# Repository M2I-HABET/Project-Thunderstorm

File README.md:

Project Thunderstorm
==================

Project Thunderstorm aims to launch high altitude balloons into thunderstorms in order to collect data. Multiple balloons will be launched to take data points at different points in the thunderstorm and to use a mesh network to help deliver information throughout the thunderstorm.

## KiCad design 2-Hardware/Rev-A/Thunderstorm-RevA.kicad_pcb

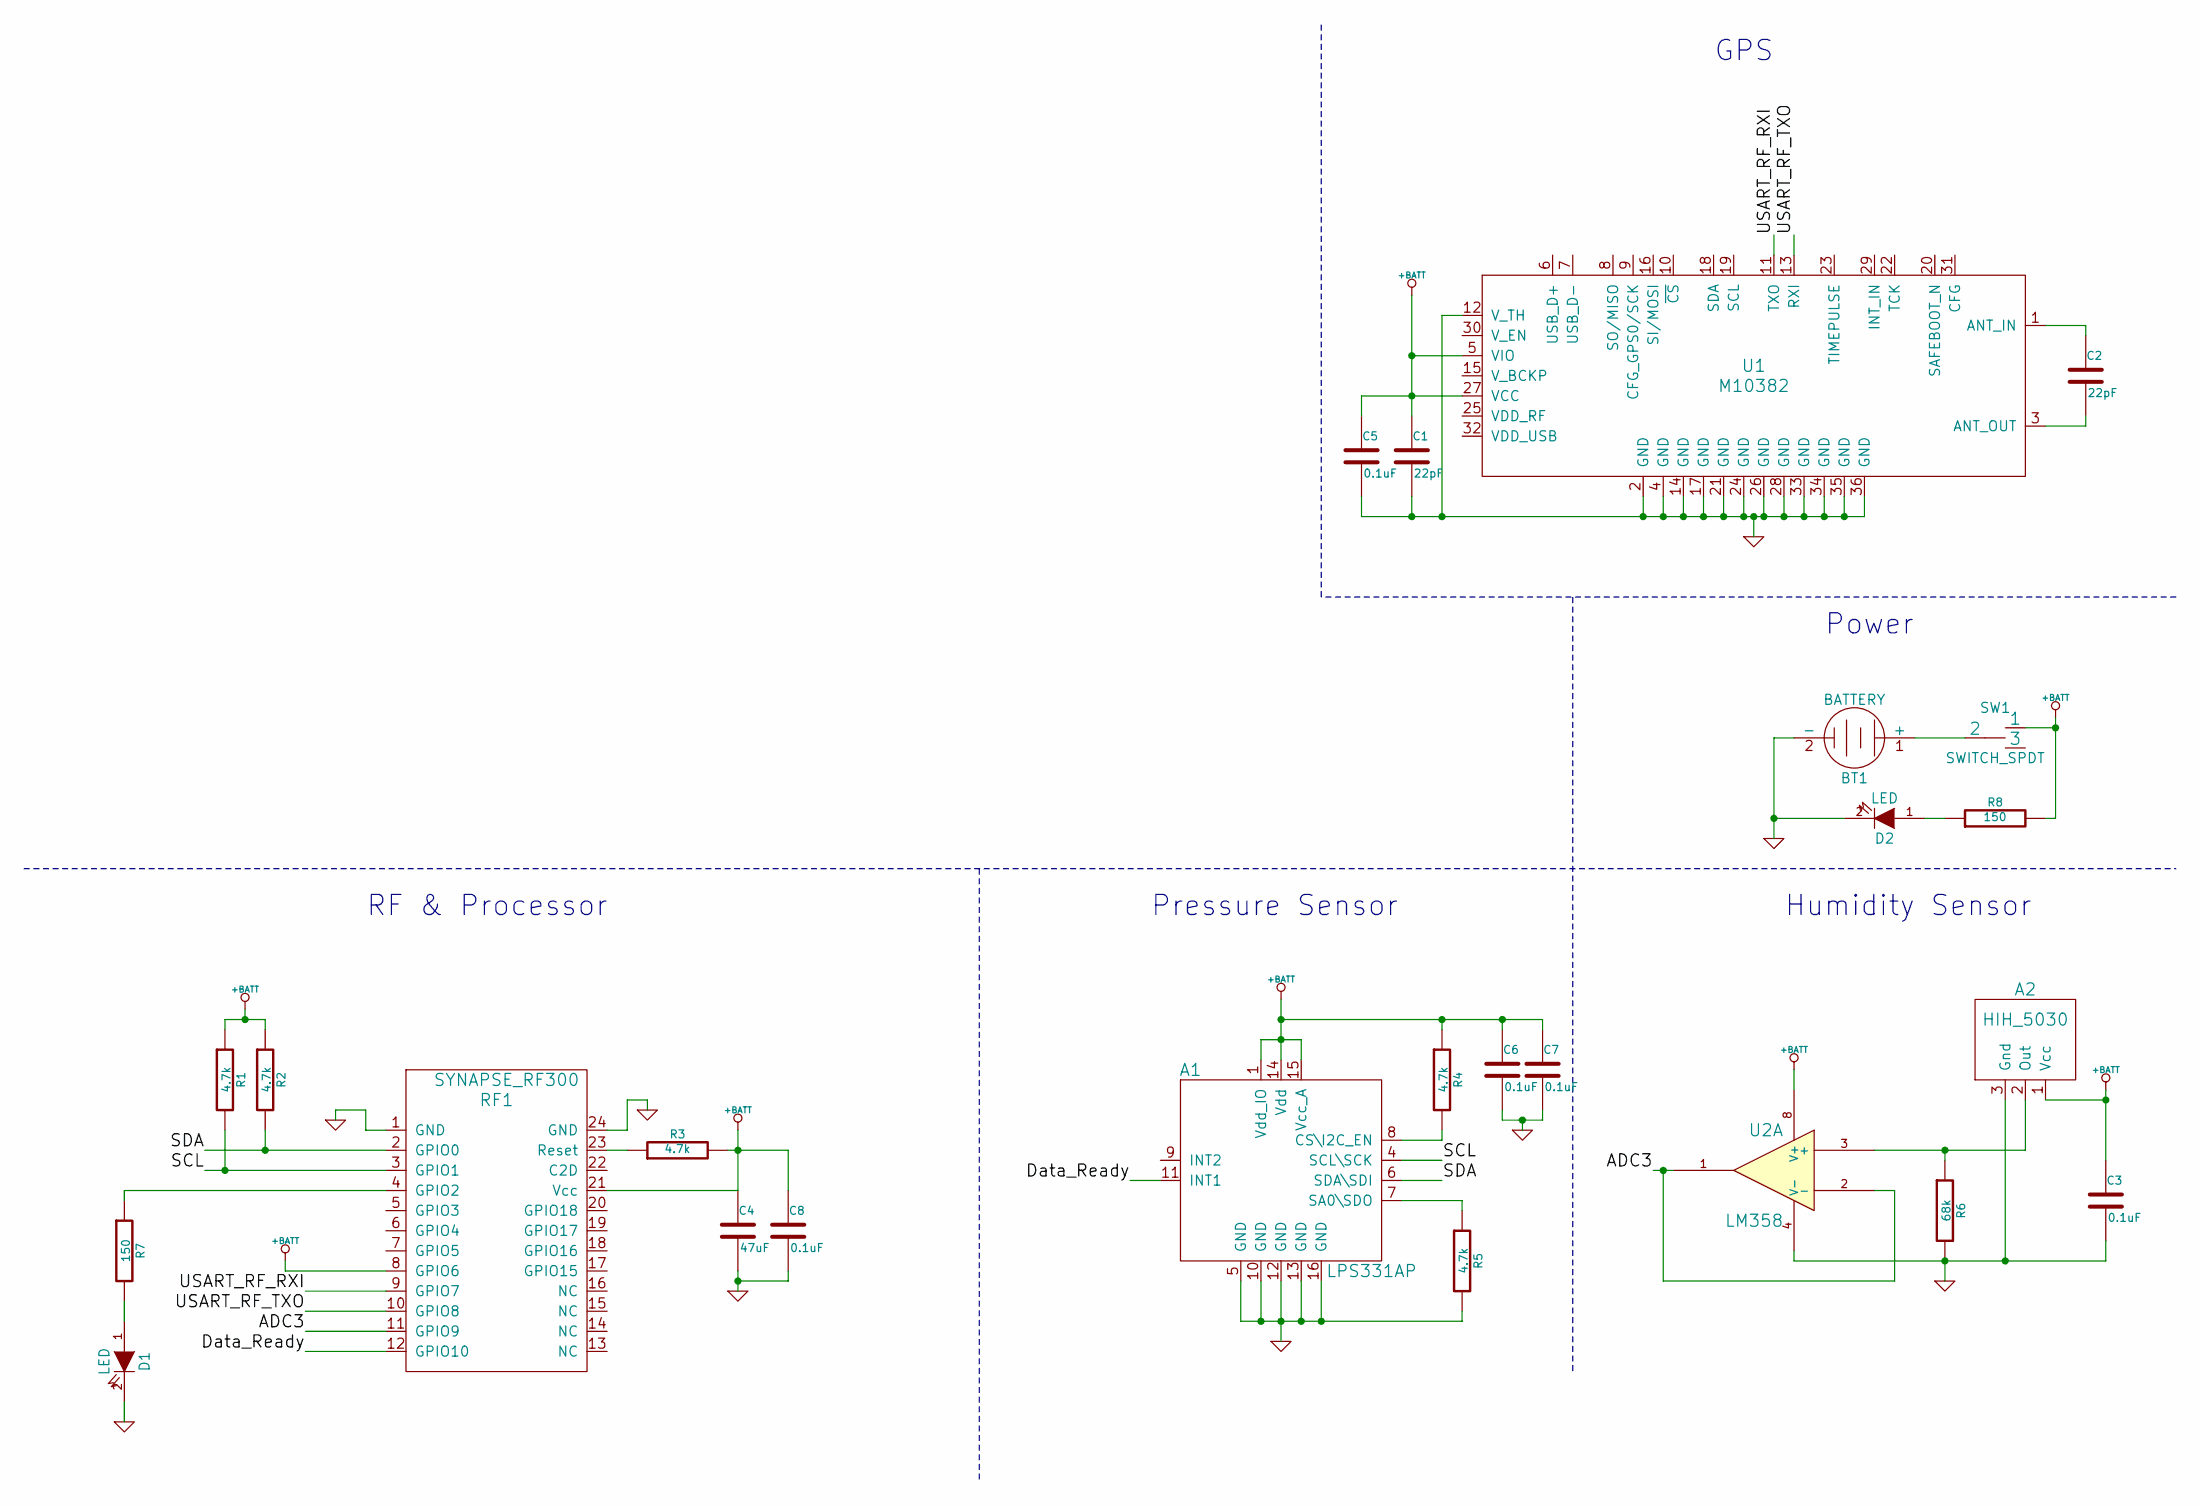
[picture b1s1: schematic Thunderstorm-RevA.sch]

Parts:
A1: LPS331AP
A2: HIH_5030
BT1: BATTERY
C1, C2: 22pF
C3, C5, C6, C7, C8: 0.1uF
C4: 47uF
D1, D2: LED
R1, R2, R3, R4, R5: 4.7k
R6: 68k
R7, R8: 150
RF1: SYNAPSE_RF300
SW1: SWITCH_SPDT
U1: M10382
U2: LM358

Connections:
+BATT: A1.1 (Vdd_IO), A1.14 (Vdd), A1.15 (Vcc_A), A2.1 (Vcc), C1.1, C3.1, C4.1, C5.1, C6.1, C7.1, C8.1, R1.1, R2.1, R3.2, R4.1, R8.2, RF1.8 (GPIO6), RF1.21 (Vcc), SW1.1, U1.5 (VIO), U1.27 (VCC), U2.8 (V+)
/ADC3: RF1.11 (GPIO9), U2.1, U2.2 (-)
/Data_Ready: A1.11 (INT1), RF1.12 (GPIO10)
/SCL: A1.4 (SCL\SCK), R1.2, RF1.3 (GPIO1)
/SDA: A1.6 (SDA\SDI), R2.2, RF1.2 (GPIO0)
/USART_RF_RXI: RF1.9 (GPIO7), U1.11 (TXO)
/USART_RF_TXO: RF1.10 (GPIO8), U1.13 (RXI)
GND: A1.5 (GND), A1.10 (GND), A1.12 (GND), A1.13 (GND), A1.16 (GND), A2.3 (Gnd), BT1.2 (-), C1.2, C3.2, C4.2, C5.2, C6.2, C7.2, C8.2, D1.2 (K), D2.2 (K), R5.2, R6.2, RF1.1 (GND), RF1.24 (GND), U1.2 (GND), U1.4 (GND), U1.12 (V_TH), U1.14 (GND), U1.17 (GND), U1.21 (GND), U1.24 (GND), U1.26 (GND), U1.28 (GND), U1.33 (GND), U1.34 (GND), U1.35 (GND), U1.36 (GND), U2.4 (V-)
unnamed: A1.7 (SA0\SDO), R5.1
unnamed: A1.8 (CS\I2C_EN), R4.2
unnamed: C2.2, U1.3 (ANT_OUT)
unnamed: C2.1, U1.1 (ANT_IN)
unnamed: A2.2 (Out), R6.1, U2.3 (+)
unnamed: R7.1, RF1.4 (GPIO2)
unnamed: D1.1 (A), R7.2
unnamed: D2.1 (A), R8.1
unnamed: R3.1, RF1.23 (Reset)
unnamed: BT1.1 (+), SW1.2

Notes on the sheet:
Humidity Sensor
GPS
RF & Processor
Power
Pressure Sensor

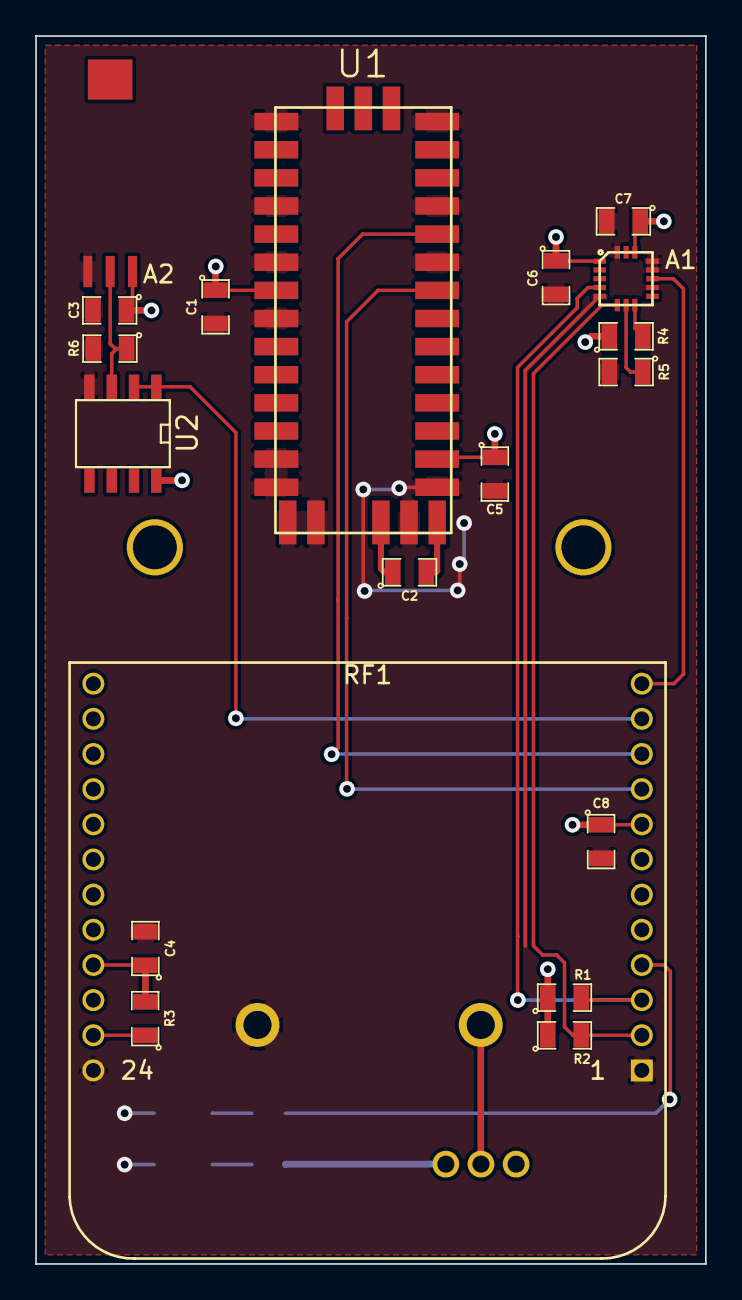
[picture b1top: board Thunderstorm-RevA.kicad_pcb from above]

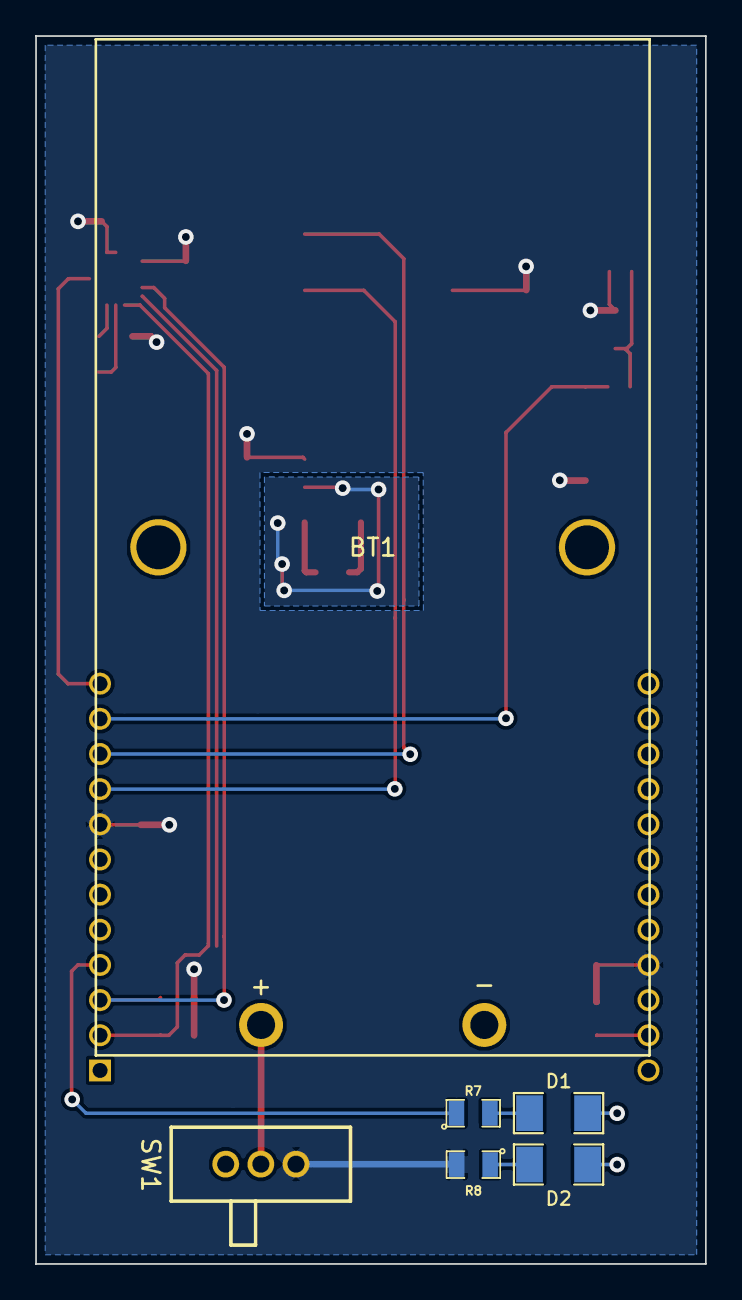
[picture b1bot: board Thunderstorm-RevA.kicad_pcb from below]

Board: 2 copper layers, 38.1 x 69.8 mm, 25 parts (6 on the bottom side), 18 nets.

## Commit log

2014-05-20 Datasheets for the parts used.
2014-05-20 Completed revision A of the schematic.
2014-05-27 Changed humidity sensor part number to be correct (fixes #1). Updated op-amp circuit to fix incorrect negative terminal wiring (fixes #3). Changed ADC input for humidity sensor to connect Vref to Vcc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
2014-05-28 Added firmware initial commit
    Added an initial commit for the firmware, not even close to being
    something usable, but sets up the folder.
2014-05-28 Fixed datasheet name for humidity sensor.
2014-05-28 Added datasheet for transceiver.
2014-05-28 Added LEDs for power and diagnostics. (Fixes #4).
2014-05-30 Added decoupling capacitors.
2014-05-30 Initial (unrouted) layout of PCB.
2014-06-02 Added decoupling capacitor.
2014-06-02 Routed traces and created board outline.
2014-06-02 Manufacturing outputs for running through FreeDFM.
2014-08-10 Updated circuit board.
2015-02-04 Created new gerber files, determined board size
2015-03-18 Initial revision for link quality firmware
2020-04-24 Replaced the datasheets with hw we are actually using.
2020-04-24 Fixed spelling error
2020-05-07 Small code changes, fixed temp probe
2020-05-07 Left something out of the last change. Oops
2020-07-10 Added enclosure solidworks files
2020-07-10 THIS time it added the changed CircuitPython script
2020-07-10 Typo
2020-07-13 Updated solidworks parts after first test print
2020-07-20 Redid thunderstorm enclosures in solidworks. Also cleaned up ThunderStorm.py code and added battery voltage to data line
2021-07-03 Update README.md
    Revised to reflect a restructuring of HABET GitHub repos
